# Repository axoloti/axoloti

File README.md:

# Axoloti

by Johannes Taelman

johannes.taelman@gmail.com

Axoloti is a platform for sketching music-DSP algorithms running on standalone hardware.

[Axoloti website](http://www.axoloti.com)

documentation: in the folder doc/

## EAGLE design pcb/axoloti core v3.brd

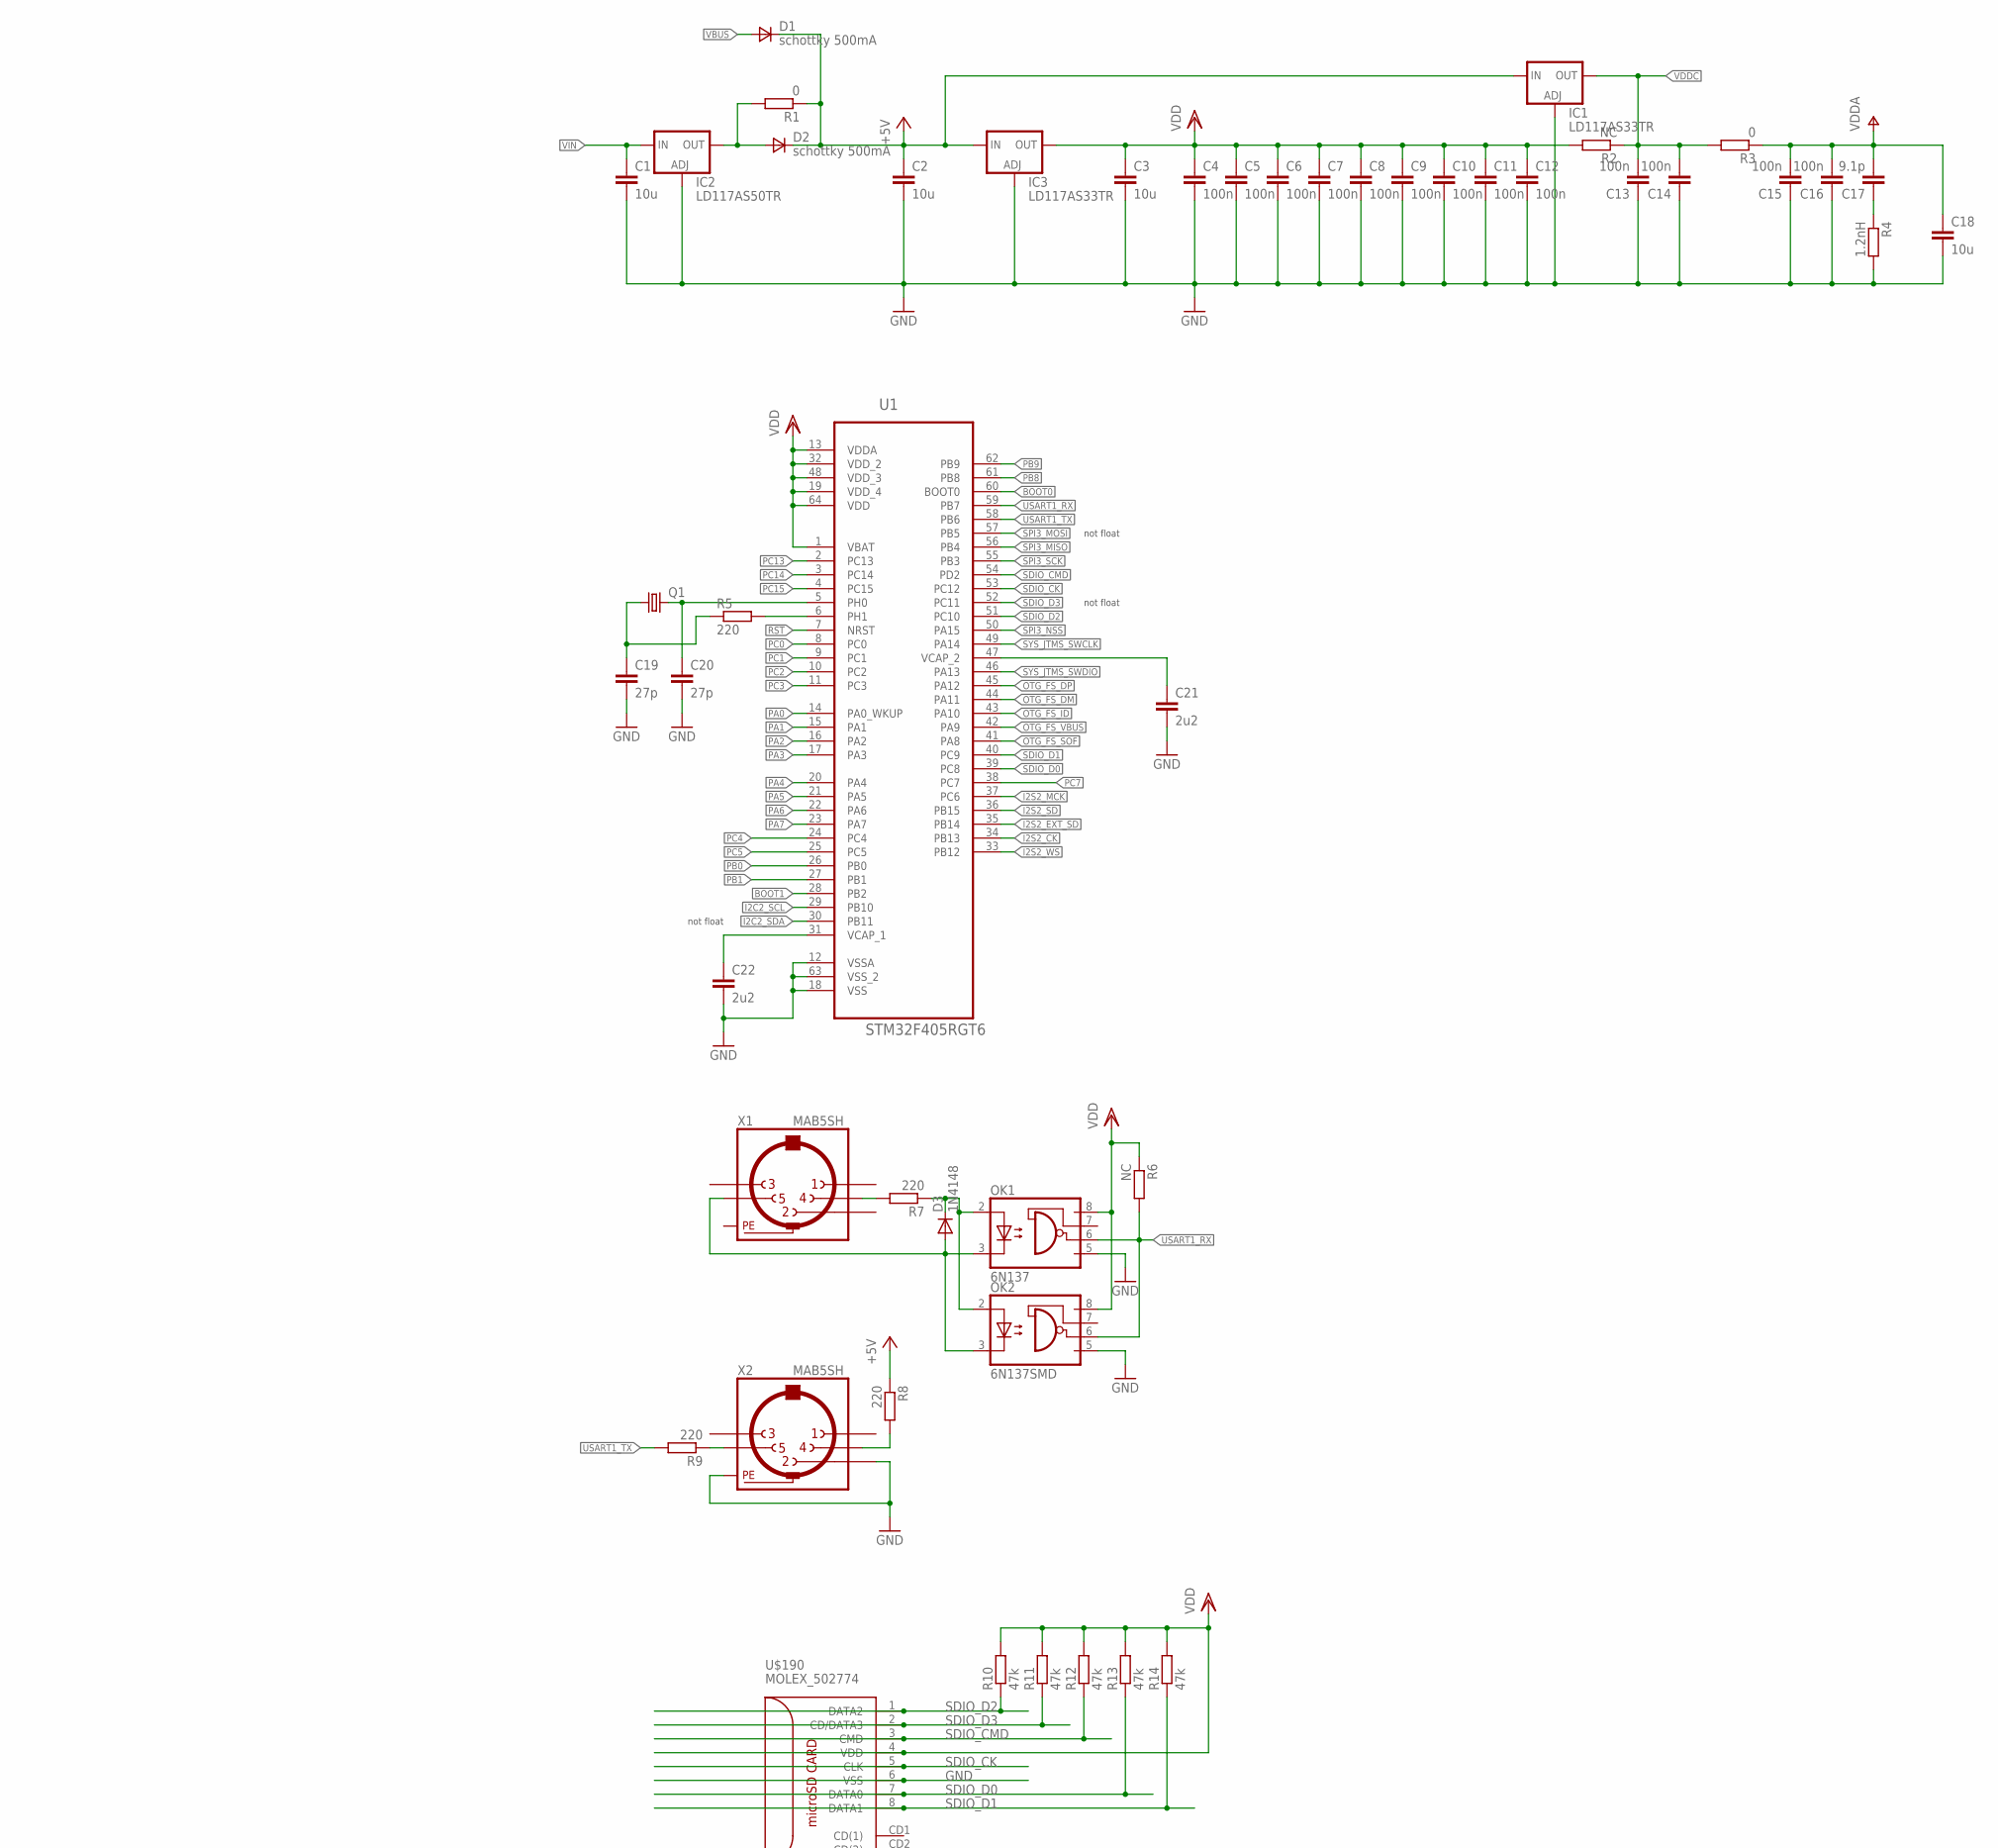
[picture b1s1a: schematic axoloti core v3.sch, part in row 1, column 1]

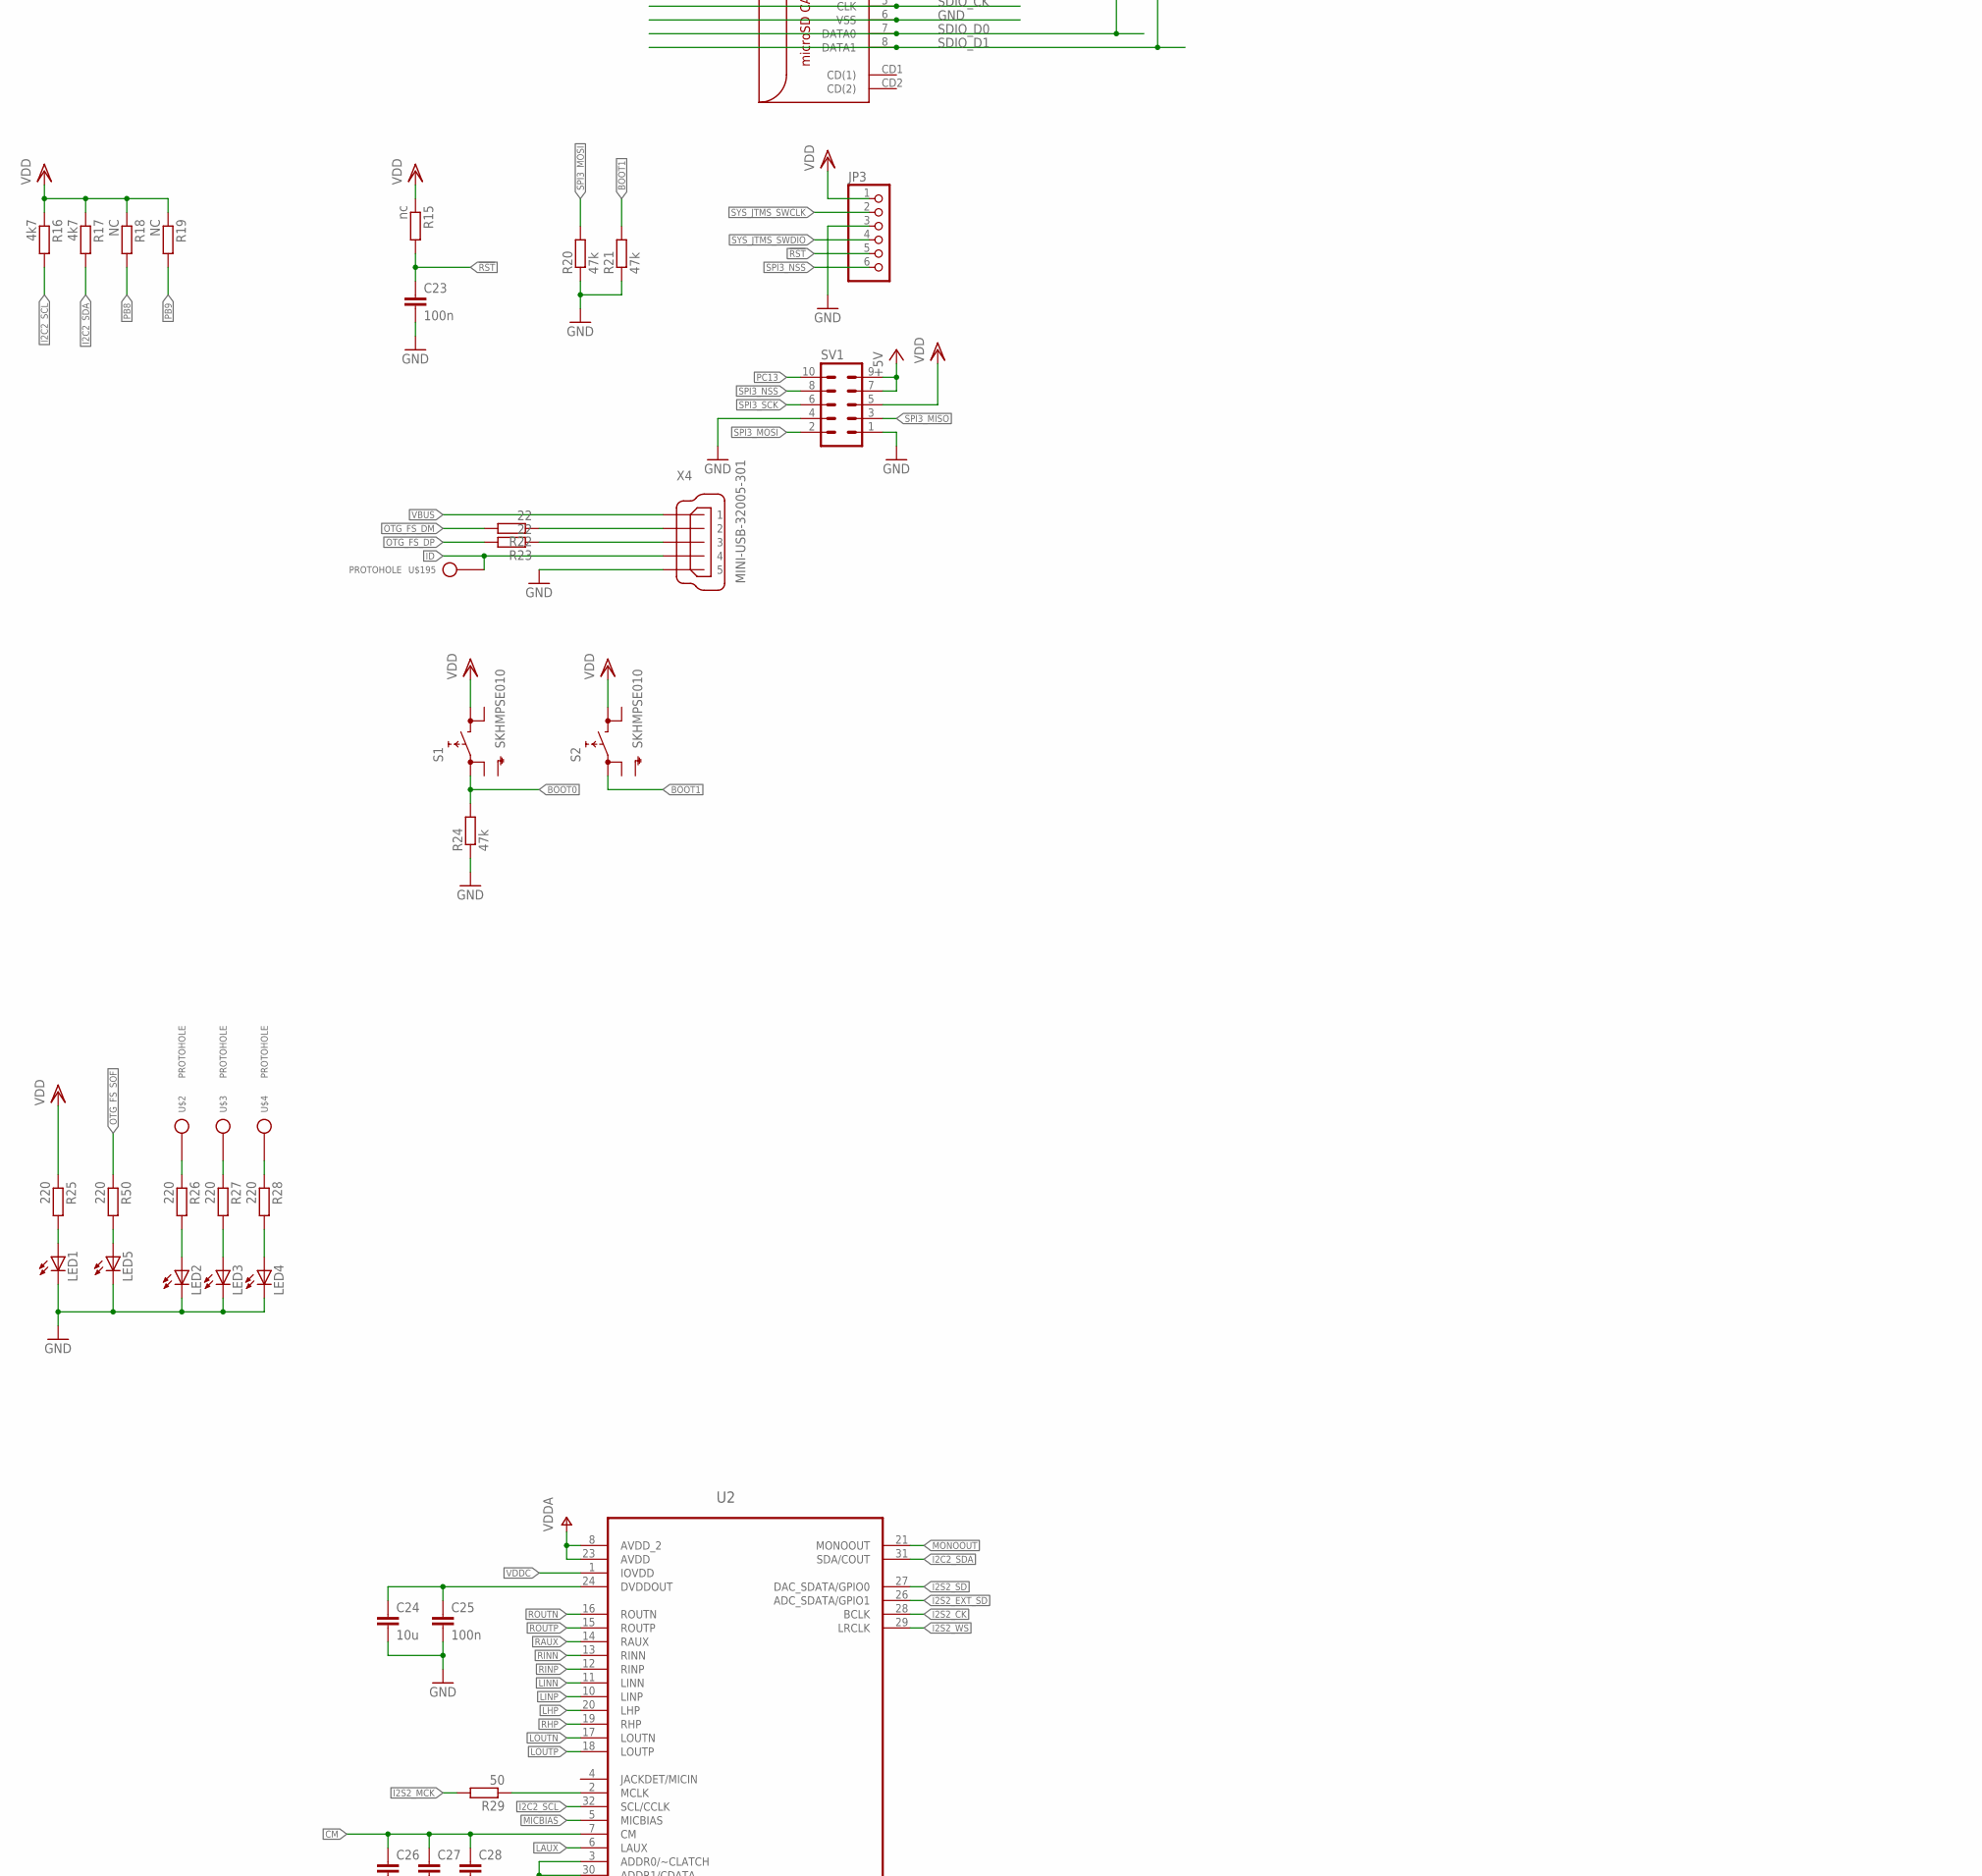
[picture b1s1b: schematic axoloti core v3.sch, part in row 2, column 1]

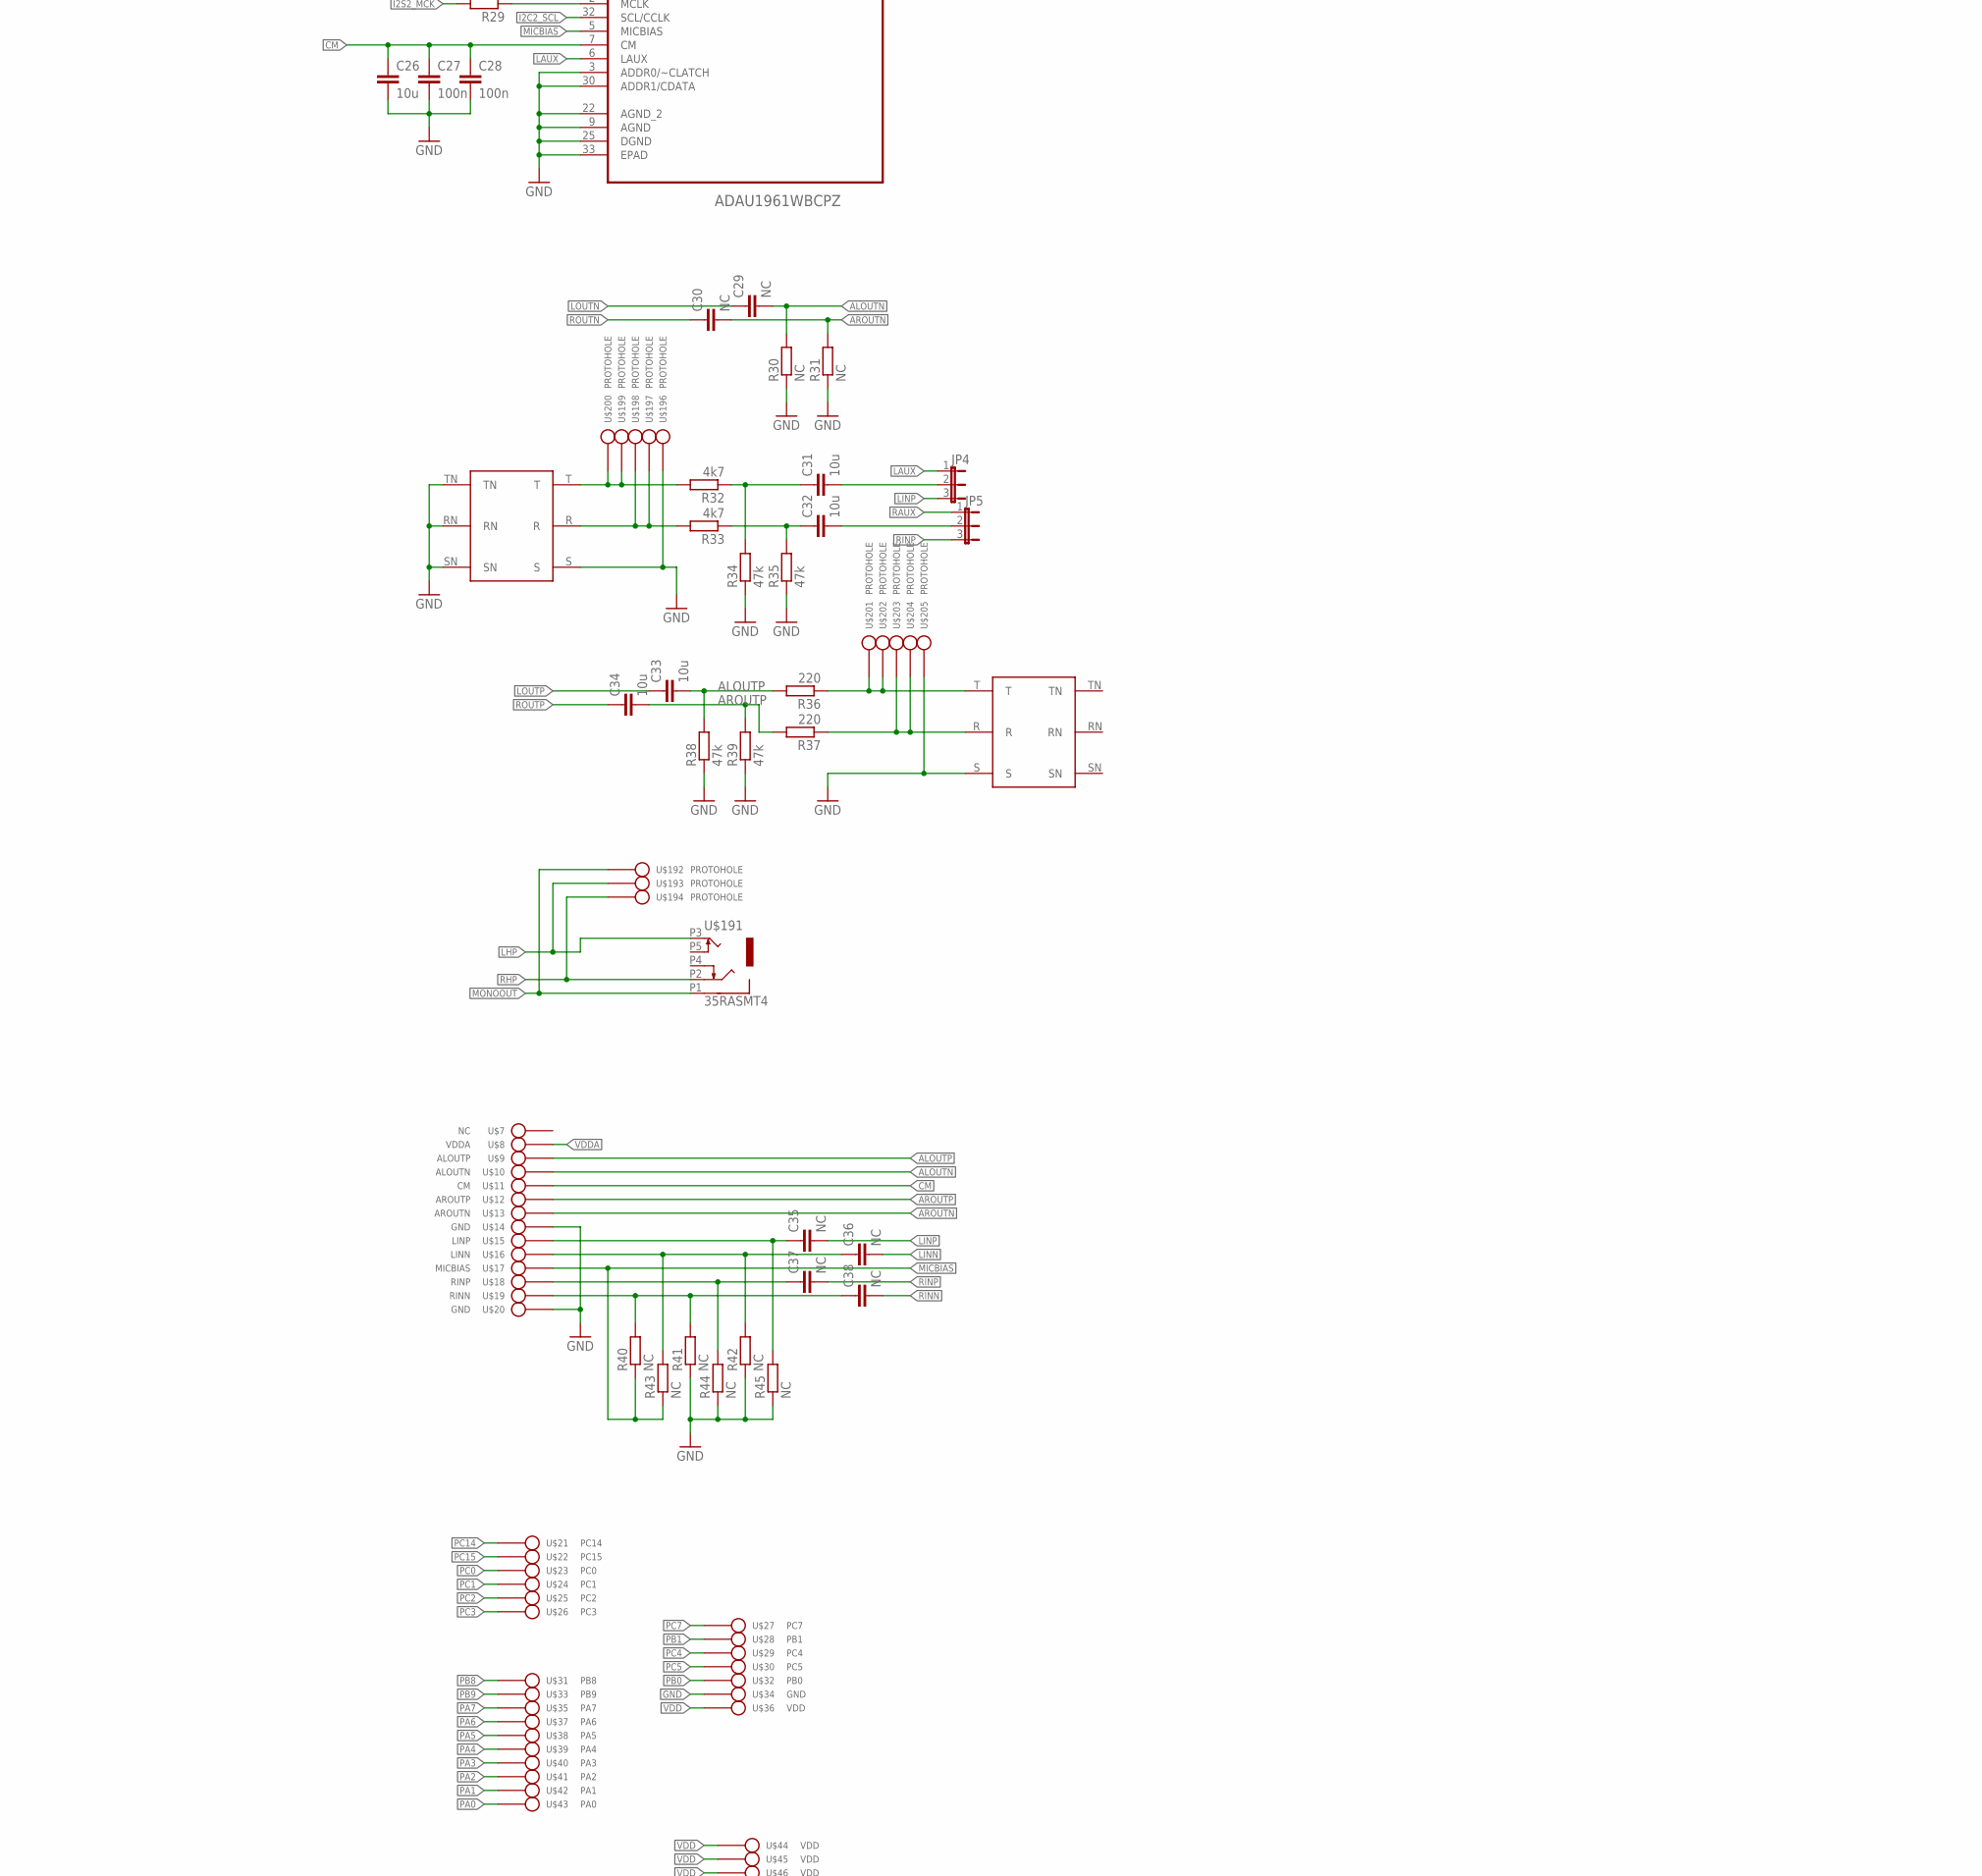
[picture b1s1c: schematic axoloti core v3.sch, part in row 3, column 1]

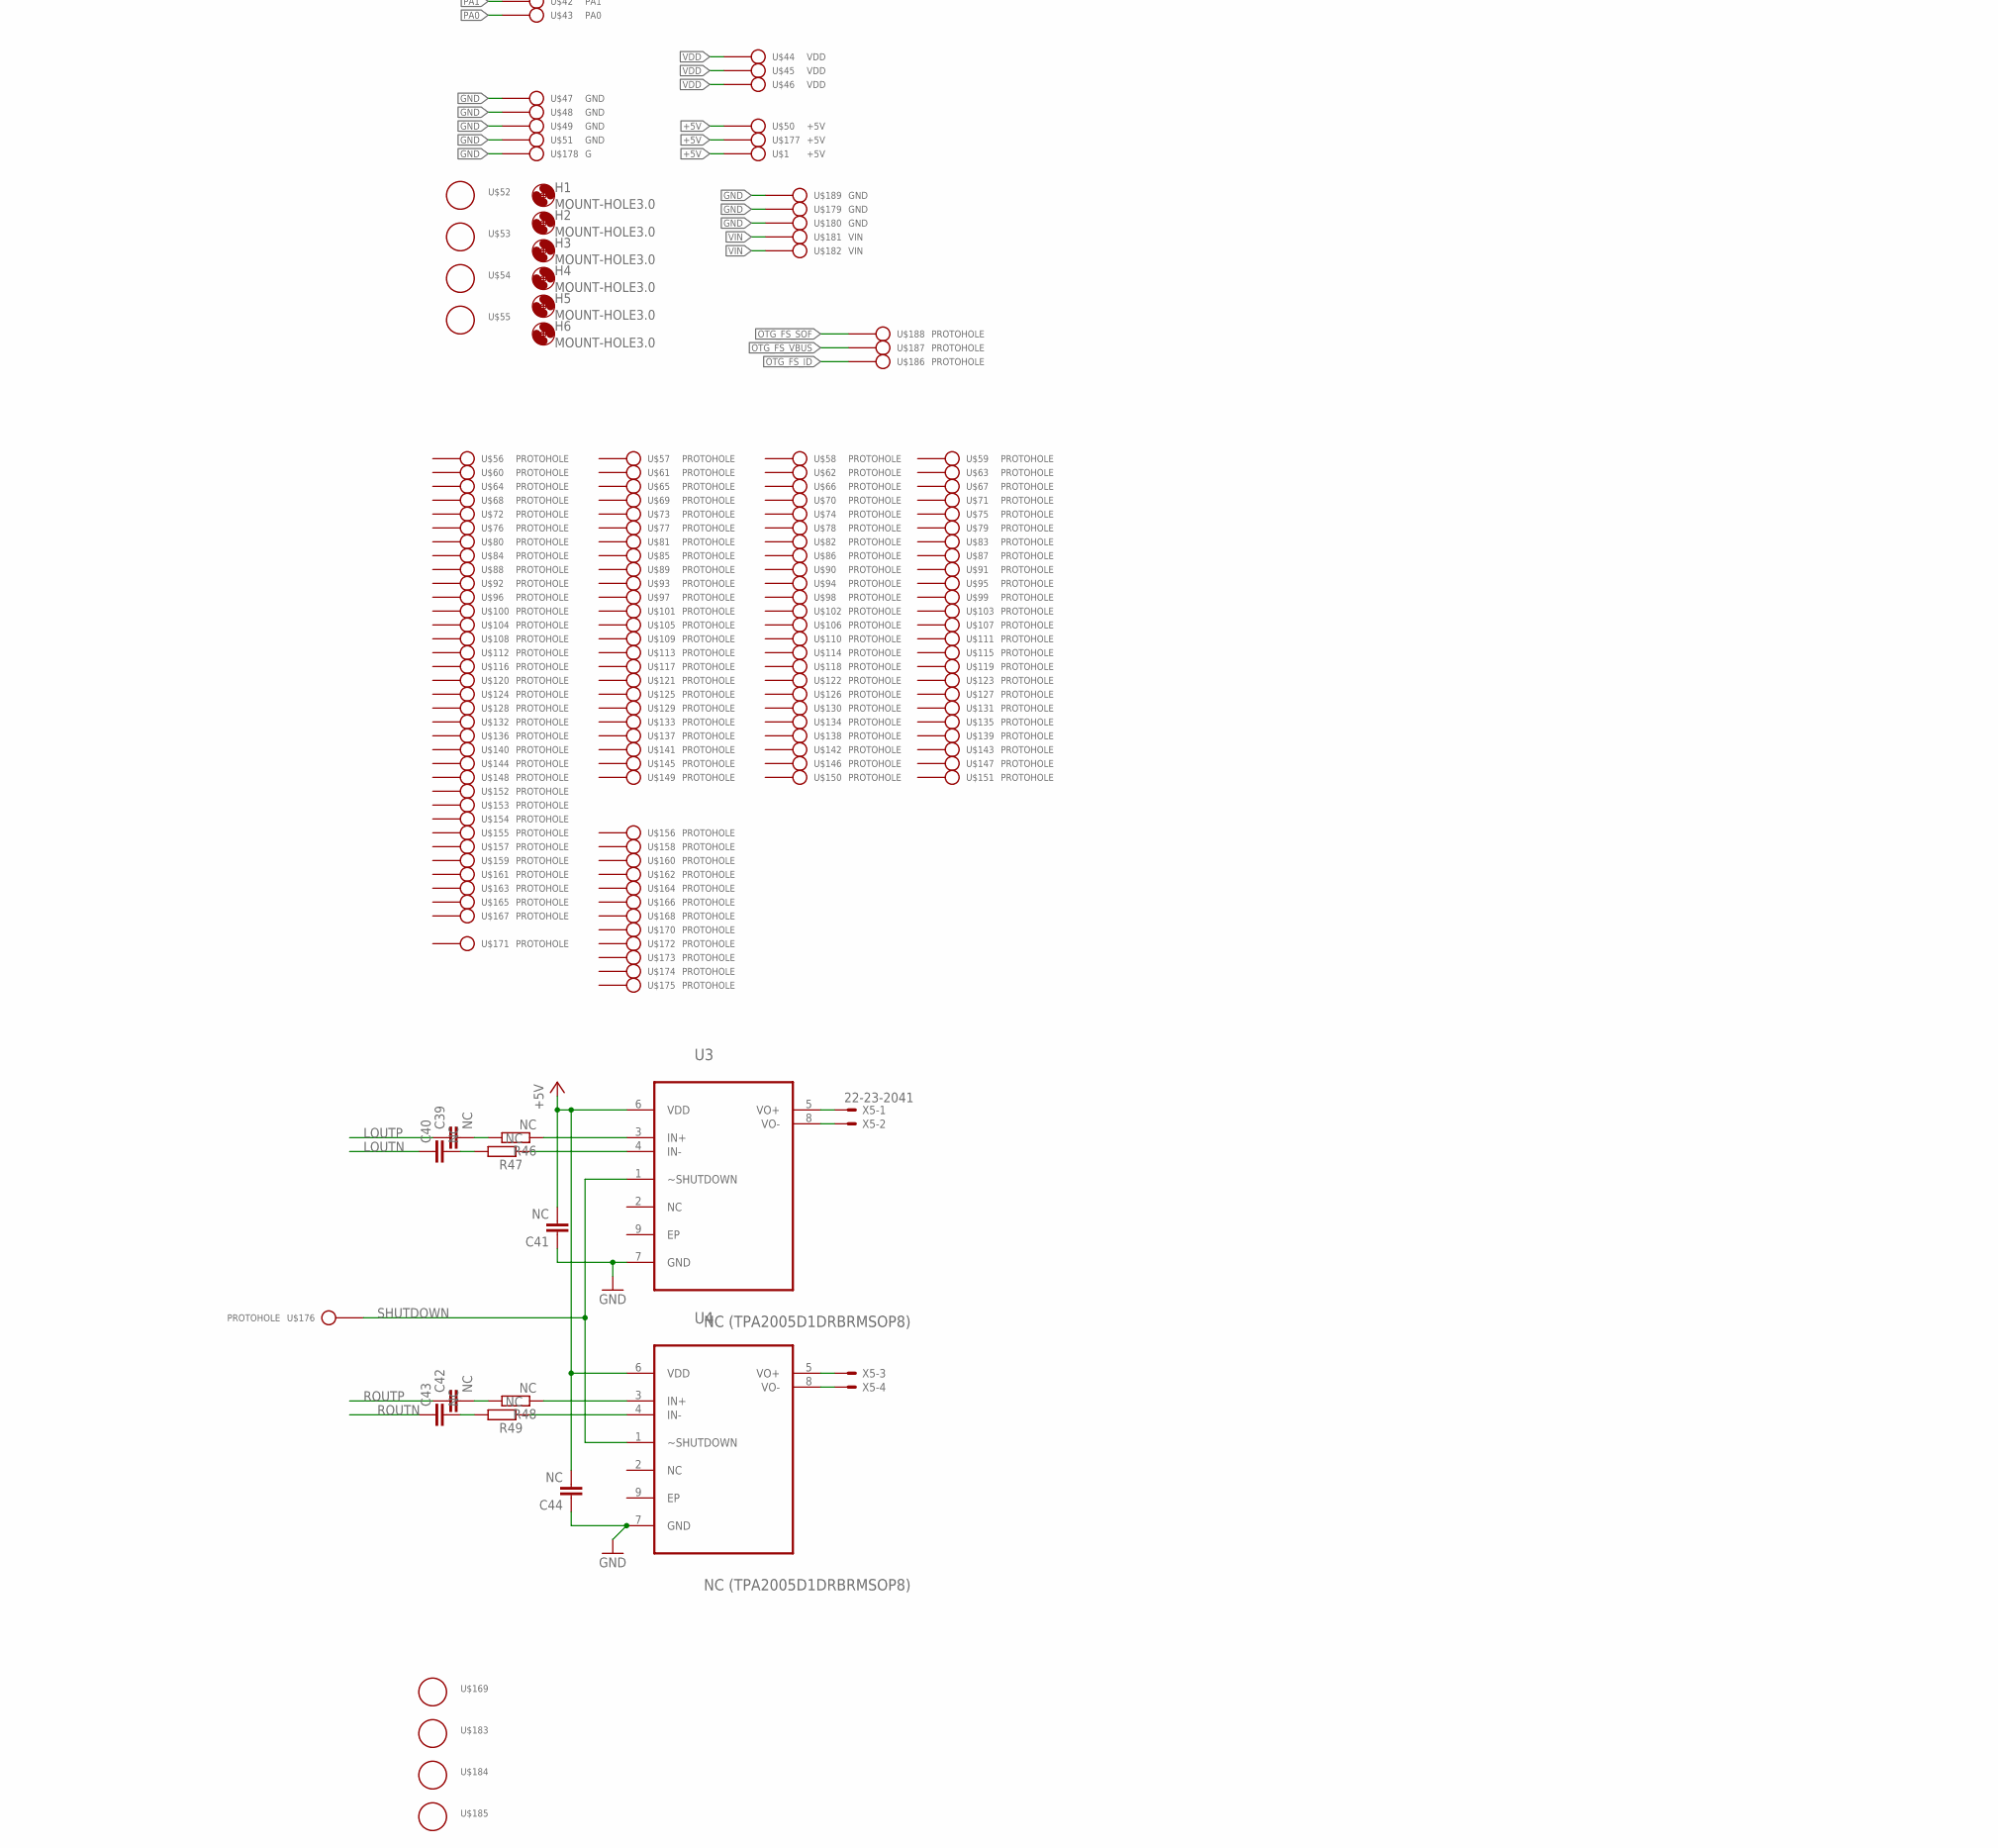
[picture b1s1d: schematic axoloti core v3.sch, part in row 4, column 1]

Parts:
C1, C2, C3, C18, C24, C26, C31, C32, C33, C34: 10u; C0805
C4, C5, C6, C7, C8, C9, C10, C11, C12, C13, C14, C15, C16, C23, C25, C27, C28: 100n; C0603
C17: 9.1p; C0603
C19, C20: 27p; C0603
C21, C22: 2u2; C0603
C29, C30, C35, C36, C37, C38: NC; C0805
C39, C40, C41, C42, C43, C44: NC; C0603
D1: schottky 500mA; SOD323
D2: schottky 500mA; SOD323; MPN CDSOD323-T05C
D3: 1N4148; SOD323-W
H1, H2, H3, H4, H5, H6: MOUNT-HOLE3.0; 3,0
IC1, IC3: LD117AS33TR; SOT223
IC2: LD117AS50TR; SOT223
JP3: PINHD-1X6; 1X06
JP4, JP5: JP2E; JP2
LED1, LED2, LED3, LED4, LED5: LEDSML0603; SML0603
OK1: 6N137; DIL08
OK2: 6N137SMD; DIL8-SMD
Q1: CRYSTALSM49; SM49
R1, R3: 0; R0603
R2, R6, R18, R19, R30, R31, R40, R41, R42, R43, R44, R45, R46, R47, R48, R49: NC; R0603
R4: 1.2nH; R0603
R5, R7, R8, R9, R25, R26, R27, R28, R36, R37, R50: 220; R0603
R10, R11, R12, R13, R14, R20, R21, R24, R34, R35, R38, R39: 47k; R0603
R15: nc; R0603
R16, R17, R32, R33: 4k7; R0603
R22, R23: 22; R0603
R29: 50; R0603
S1, S2: SKHMPSE010; SKHMPXE010
SV1: ML10
U1: STM32F405RGT6; QFP50P1200X1200X160-64N
U2: ADAU1961WBCPZ; QFN50P500X500X100-33N
U3, U4: NC (TPA2005D1DRBRMSOP8); MSOP8
U$1, U$50, U$177: +5V; PROTOHOLE_NAMED
U$2, U$3, U$4, U$56, U$57, U$58, U$59, U$60, U$61, U$62, U$63, U$64, U$65, U$66, U$67, U$68, U$69, U$70, U$71, U$72, U$73, U$74, U$75, U$76, U$77, U$78, U$79, U$80, U$81, U$82, U$83, U$84, U$85, U$86, U$87, U$88, U$89, U$90, U$91, U$92, U$93, U$94, U$95, U$96, U$97, U$98, U$99, U$100, U$101, U$102, U$103, U$104, U$105, U$106, U$107, U$108, U$109, U$110, U$111, U$112, U$113, U$114, U$115, U$116, U$117, U$118, U$119, U$120, U$121, U$122, U$123, U$124, U$125, U$126, U$127, U$128, U$129, U$130, U$131, U$132, U$133, U$134, U$135, U$136, U$137, U$138, U$139, U$140, U$141, U$142, U$143, U$144, U$145, U$146, U$147, U$148, U$149, U$150, U$151, U$152, U$153, U$154, U$155, U$156, U$157, U$158, U$159, U$160, U$161, U$162, U$163, U$164, U$165, U$166, U$167, U$168, U$170, U$171, U$172, U$173, U$174, U$175, U$176, U$186, U$187, U$188, U$192, U$193, U$194, U$195, U$196, U$197, U$198, U$199, U$200, U$201, U$202, U$203, U$204, U$205: PROTOHOLE
U$5, U$6: JACK63
U$7: NC; PROTOHOLE_NAMED
U$8: VDDA; PROTOHOLE_NAMED
U$9: ALOUTP; PROTOHOLE_NAMED
U$10: ALOUTN; PROTOHOLE_NAMED
U$11: CM; PROTOHOLE_NAMED
U$12: AROUTP; PROTOHOLE_NAMED
U$13: AROUTN; PROTOHOLE_NAMED
U$14, U$20, U$34, U$47, U$48, U$49, U$51, U$179, U$180, U$189: GND; PROTOHOLE_NAMED
U$15: LINP; PROTOHOLE_NAMED
U$16: LINN; PROTOHOLE_NAMED
U$17: MICBIAS; PROTOHOLE_NAMED
U$18: RINP; PROTOHOLE_NAMED
U$19: RINN; PROTOHOLE_NAMED
U$21: PC14; PROTOHOLE_NAMED
U$22: PC15; PROTOHOLE_NAMED
U$23: PC0; PROTOHOLE_NAMED
U$24: PC1; PROTOHOLE_NAMED
U$25: PC2; PROTOHOLE_NAMED
U$26: PC3; PROTOHOLE_NAMED
U$27: PC7; PROTOHOLE_NAMED
U$28: PB1; PROTOHOLE_NAMED
U$29: PC4; PROTOHOLE_NAMED
U$30: PC5; PROTOHOLE_NAMED
U$31: PB8; PROTOHOLE_NAMED
U$32: PB0; PROTOHOLE_NAMED
U$33: PB9; PROTOHOLE_NAMED
U$35: PA7; PROTOHOLE_NAMED
U$36, U$44, U$45, U$46: VDD; PROTOHOLE_NAMED
U$37: PA6; PROTOHOLE_NAMED
U$38: PA5; PROTOHOLE_NAMED
U$39: PA4; PROTOHOLE_NAMED
U$40: PA3; PROTOHOLE_NAMED
U$41: PA2; PROTOHOLE_NAMED
U$42: PA1; PROTOHOLE_NAMED
U$43: PA0; PROTOHOLE_NAMED
U$52, U$53, U$54, U$55, U$169, U$183, U$184, U$185: FIDUCIAL-1
U$178: G; PROTOHOLE_NAMED
U$181, U$182: VIN; PROTOHOLE_NAMED
U$190: MOLEX_502774
U$191: 35RASMT4; 35RASMT4BHNTR
X1, X2: MAB5SH
X4: MINI-USB-32005-301; 32005-301
X5: 22-23-2041

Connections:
!RST: C23.1, JP3.5, R15.2, U1.7 (NRST)
+5V: C2.1, C41.2, C44.2, D1.1 (C), D2.1 (C), IC1.3 (IN), IC3.3 (IN), R1.1, R8.1, SV1.7, SV1.9, U3.6 (VDD), U4.6 (VDD), U$1.P$1, U$50.P$1, U$177.P$1
ALOUTN: C29.2, R30.2, U$10.P$1
ALOUTP: C33.2, R36.2, R38.2, U$9.P$1
AROUTN: C30.2, R31.2, U$13.P$1
AROUTP: C34.2, R37.2, R39.2, U$12.P$1
BOOT0: R24.2, S1.1 (1.1), U1.60 (BOOT0)
BOOT1: R21.2, S2.1 (1.1), U1.28 (PB2)
CM: C26.1, C27.1, C28.1, U2.7 (CM), U$11.P$1
DVDDOUT: C24.1, C25.1, U2.24 (DVDDOUT)
GND: C1.2, C2.2, C3.2, C4.2, C5.2, C6.2, C7.2, C8.2, C9.2, C10.2, C11.2, C12.2, C13.1, C14.1, C15.1, C16.1, C18.2, C19.2, C20.2, C21.2, C22.2, C23.2, C24.2, C25.2, C26.2, C27.2, C28.2, C41.1, C44.1, IC1.1 (ADJ), IC2.1 (ADJ), IC3.1 (ADJ), JP3.3, LED1.C, LED2.C, LED3.C, LED4.C, LED5.C, OK1.5 (GND), OK2.5 (GND), R4.2, R20.1, R21.1, R24.1, R30.1, R31.1, R34.1, R35.1, R38.1, R39.1, R41.1, R42.1, R44.1, R45.1, SV1.1, SV1.4, U1.12 (VSSA), U1.18 (VSS), U1.63 (VSS_2), U2.3 (ADDR0/~CLATCH), U2.9 (AGND), U2.22 (AGND_2), U2.25 (DGND), U2.30 (ADDR1/CDATA), U2.33 (EPAD), U3.7 (GND), U4.7 (GND), U$5.RN, U$5.S, U$5.SN, U$5.TN, U$6.S, U$14.P$1, U$20.P$1, U$34.P$1, U$47.P$1, U$48.P$1, U$49.P$1, U$51.P$1, U$178.P$1, U$179.P$1, U$180.P$1, U$189.P$1, U$190.6 (VSS), U$196.P$1, U$205.P$1, X2.2, X2.PE, X2.PE@ (PE), X4.5
I2C2_SCL: R16.2, U1.29 (PB10), U2.32 (SCL/CCLK)
I2C2_SDA: R17.2, U1.30 (PB11), U2.31 (SDA/COUT)
I2S2_CK: U1.34 (PB13), U2.28 (BCLK)
I2S2_EXT_SD: U1.35 (PB14), U2.26 (ADC_SDATA/GPIO1)
I2S2_MCK: R29.2, U1.37 (PC6)
I2S2_SD: U1.36 (PB15), U2.27 (DAC_SDATA/GPIO0)
I2S2_WS: U1.33 (PB12), U2.29 (LRCLK)
ID: U$195.P$1, X4.4
LAUX: JP4.1, U2.6 (LAUX)
LHP: U2.20 (LHP), U$191.P3 (T), U$193.P$1
LINN: C36.2, U2.11 (LINN)
LINP: C35.2, JP4.3, U2.10 (LINP)
LOUTN: C29.1, C40.1, U2.17 (LOUTN)
LOUTP: C33.1, C39.1, U2.18 (LOUTP)
MICBIAS: R40.1, R43.1, U2.5 (MICBIAS), U$17.P$1
MONOOUT: U2.21 (MONOOUT), U$191.P1 (S), U$192.P$1
unnamed: LED1.A, R25.2
unnamed: C37.1, R44.2, U$18.P$1
unnamed: C38.1, R40.2, R41.2, U$19.P$1
unnamed: C36.1, R42.2, R43.2, U$16.P$1
unnamed: C35.1, R45.2, U$15.P$1
unnamed: R36.1, U$6.T, U$201.P$1, U$202.P$1
unnamed: R37.1, U$6.R, U$203.P$1, U$204.P$1
unnamed: R5.2, U1.6 (PH1)
unnamed: C17.1, R4.1
unnamed: R29.1, U2.2 (MCLK)
unnamed: C19.1, Q1.1, R5.1
unnamed: C20.1, Q1.2, U1.5 (PH0)
unnamed: R22.1, X4.2
unnamed: R23.1, X4.3
unnamed: U3.5 (VO+), X5.1
unnamed: U3.8 (VO-), X5.2
unnamed: LED5.A, R50.2
unnamed: D2.2 (A), IC2.4 (OUT), R1.2
unnamed: R26.1, U$2.P$1
unnamed: R27.1, U$3.P$1
unnamed: R28.1, U$4.P$1
unnamed: C31.2, JP4.2
unnamed: U4.8 (VO-), X5.4
unnamed: U4.5 (VO+), X5.3
unnamed: R46.1, U3.3 (IN+)
unnamed: R47.1, U3.4 (IN-)
unnamed: C39.2, R46.2
unnamed: C40.2, R47.2
unnamed: R49.1, U4.4 (IN-)
unnamed: C42.2, R48.2
unnamed: C43.2, R49.2
unnamed: R48.1, U4.3 (IN+)
unnamed: D3.A, OK1.3 (C), OK2.3 (C), X1.5
unnamed: C32.2, JP5.2
unnamed: R32.2, U$5.T, U$199.P$1, U$200.P$1
unnamed: R7.2, X1.4
unnamed: R33.2, U$5.R, U$197.P$1, U$198.P$1
unnamed: C32.1, R33.1, R35.2
unnamed: C31.1, R32.1, R34.2
unnamed: LED2.A, R26.2
unnamed: LED3.A, R27.2
unnamed: LED4.A, R28.2
unnamed: D3.C, OK1.2 (A), OK2.2 (A), R7.1
unnamed: R8.2, X2.4
unnamed: R9.1, X2.5
OTG_FS_DM: R22.2, U1.44 (PA11)
OTG_FS_DP: R23.2, U1.45 (PA12)
OTG_FS_ID: U1.43 (PA10), U$186.P$1
OTG_FS_SOF: R50.1, U1.41 (PA8), U$188.P$1
OTG_FS_VBUS: U1.42 (PA9), U$187.P$1
PA0: U1.14 (PA0_WKUP), U$43.P$1
PA1: U1.15 (PA1), U$42.P$1
PA2: U1.16 (PA2), U$41.P$1
PA3: U1.17 (PA3), U$40.P$1
PA4: U1.20 (PA4), U$39.P$1
PA5: U1.21 (PA5), U$38.P$1
PA6: U1.22 (PA6), U$37.P$1
PA7: U1.23 (PA7), U$35.P$1
PB0: U1.26 (PB0), U$32.P$1
PB1: U1.27 (PB1), U$28.P$1
PB8: R18.2, U1.61 (PB8), U$31.P$1
PB9: R19.2, U1.62 (PB9), U$33.P$1
PC0: U1.8 (PC0), U$23.P$1
PC1: U1.9 (PC1), U$24.P$1
PC2: U1.10 (PC2), U$25.P$1
PC3: U1.11 (PC3), U$26.P$1
PC4: U1.24 (PC4), U$29.P$1
PC5: U1.25 (PC5), U$30.P$1
PC7: U1.38 (PC7), U$27.P$1
PC13: SV1.10, U1.2 (PC13)
PC14: U1.3 (PC14), U$21.P$1
PC15: U1.4 (PC15), U$22.P$1
PE: X1.PE, X1.PE@ (PE)
RAUX: JP5.1, U2.14 (RAUX)
RHP: U2.19 (RHP), U$191.P2 (R), U$194.P$1
RINN: C38.2, U2.13 (RINN)
RINP: C37.2, JP5.3, U2.12 (RINP)
ROUTN: C30.1, C43.1, U2.16 (ROUTN)
ROUTP: C34.1, C42.1, U2.15 (ROUTP)
SDIO_CK: U1.53 (PC12), U$190.5 (CLK)
SDIO_CMD: R12.1, U1.54 (PD2), U$190.3 (CMD)
SDIO_D0: R13.1, U1.39 (PC8), U$190.7 (DATA0)
SDIO_D1: R14.1, U1.40 (PC9), U$190.8 (DATA1)
SDIO_D2: R10.1, U1.51 (PC10), U$190.1 (DATA2)
SDIO_D3: R11.1, U1.52 (PC11), U$190.2 (CD/DATA3)
SHUTDOWN: U3.1 (~SHUTDOWN), U4.1 (~SHUTDOWN), U$176.P$1
SPI3_MISO: SV1.3, U1.56 (PB4)
SPI3_MOSI: R20.2, SV1.2, U1.57 (PB5)
SPI3_NSS: JP3.6, SV1.8, U1.50 (PA15)
SPI3_SCK: SV1.6, U1.55 (PB3)
SYS_JTMS_SWCLK: JP3.2, U1.49 (PA14)
SYS_JTMS_SWDIO: JP3.4, U1.46 (PA13)
USART1_RX: OK1.6 (VO), OK2.6 (VO), R6.2, U1.59 (PB7)
USART1_TX: R9.2, U1.58 (PB6)
VBUS: D1.2 (A), X4.1
VCAP1: C22.1, U1.31 (VCAP_1)
VCAP2: C21.1, U1.47 (VCAP_2)
VDD: C3.1, C4.1, C5.1, C6.1, C7.1, C8.1, C9.1, C10.1, C11.1, C12.1, IC3.4 (OUT), JP3.1, OK1.8 (VCC), OK2.8 (VCC), R2.2, R6.1, R10.2, R11.2, R12.2, R13.2, R14.2, R15.1, R16.1, R17.1, R18.1, R19.1, R25.1, S1.3 (2.1), S2.3 (2.1), SV1.5, U1.1 (VBAT), U1.13 (VDDA), U1.19 (VDD_4), U1.32 (VDD_2), U1.48 (VDD_3), U1.64 (VDD), U$36.P$1, U$44.P$1, U$45.P$1, U$46.P$1, U$190.4 (VDD)
VDDA: C15.2, C16.2, C17.2, C18.1, R3.1, U2.8 (AVDD_2), U2.23 (AVDD), U$8.P$1
VDDC: C13.2, C14.2, IC1.4 (OUT), R2.1, R3.2, U2.1 (IOVDD)
VIN: C1.1, IC2.3 (IN), U$181.P$1, U$182.P$1

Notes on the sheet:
not float

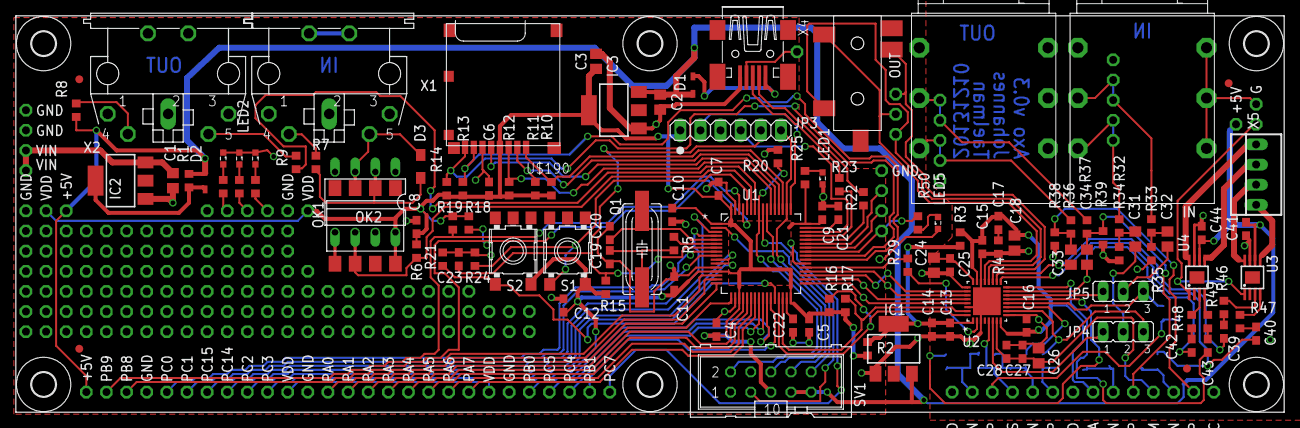
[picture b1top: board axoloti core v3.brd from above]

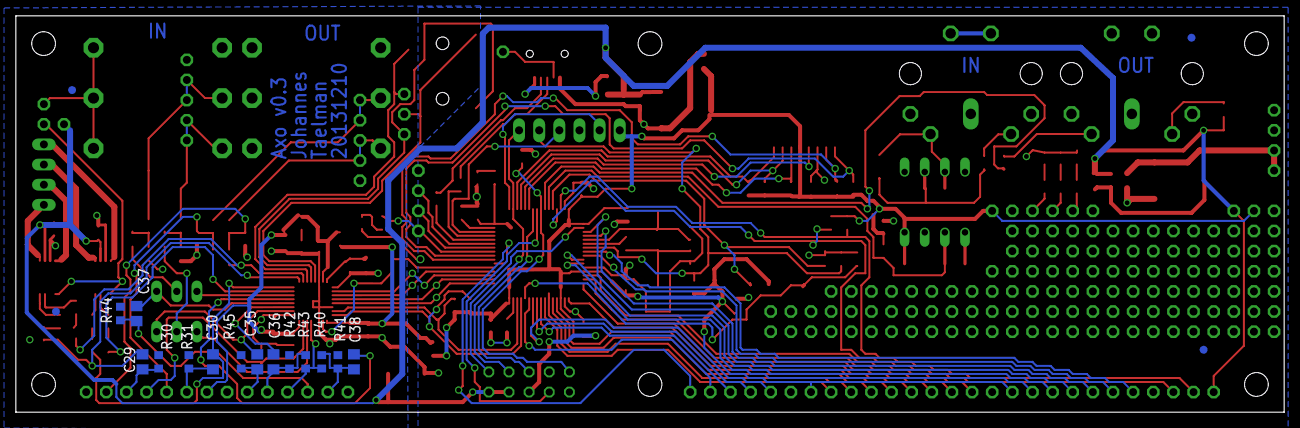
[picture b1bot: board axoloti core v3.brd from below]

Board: 2 copper layers, 160.0 x 50.0 mm, 333 parts (18 on the bottom side), 128 nets.
